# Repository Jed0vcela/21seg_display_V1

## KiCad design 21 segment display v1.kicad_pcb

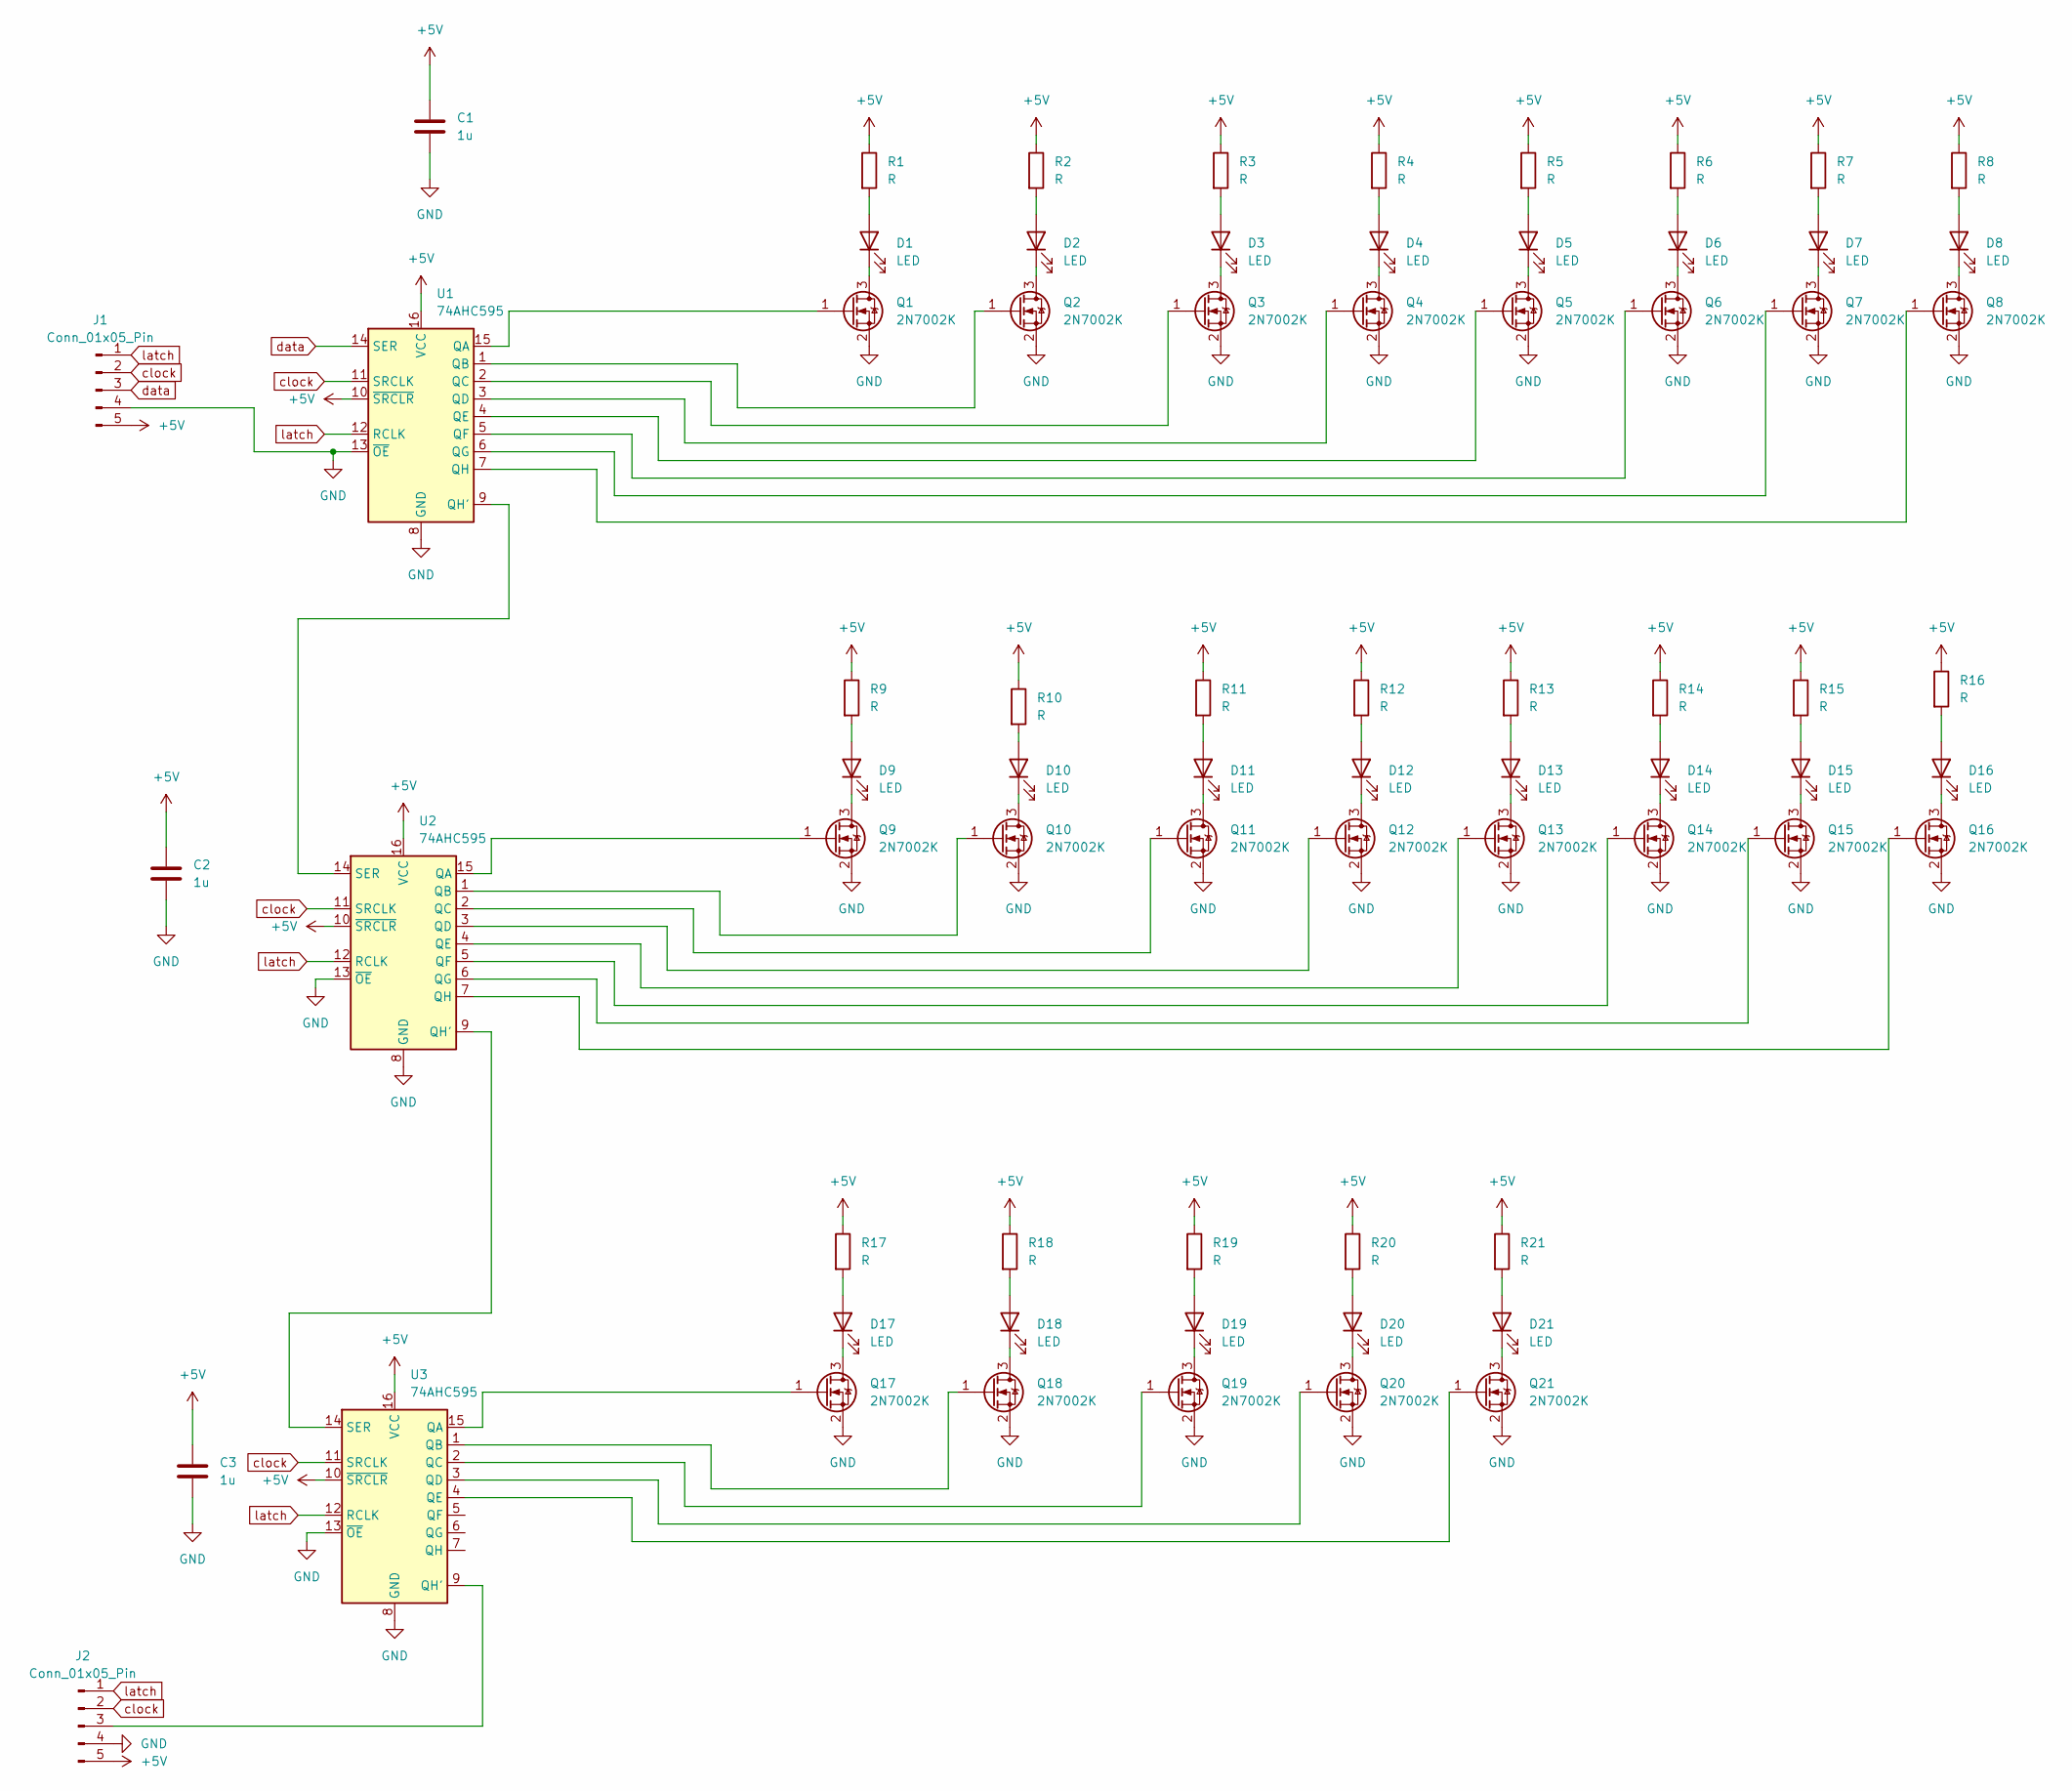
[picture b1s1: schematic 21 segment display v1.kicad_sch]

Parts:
C1, C2, C3: 1u; C_0805_2012Metric
D1, D2, D3, D4, D5, D6, D7, D8, D9, D10, D11, D12, D13, D14, D15, D16, D17, D18, D19, D20, D21: LED; LED_1210_3225Metric_Pad1.42x2.65mm_HandSolder
J1: Conn_01x05_Pin; PinHeader_1x05_P2.54mm_Horizontal
J2: Conn_01x05_Pin; PinSocket_1x05_P2.54mm_Horizontal
Q1, Q2, Q3, Q4, Q5, Q6, Q7, Q8, Q9, Q10, Q11, Q12, Q13, Q14, Q15, Q16, Q17, Q18, Q19, Q20, Q21: 2N7002K; SOT-23
R1, R2, R3, R4, R5, R6, R7, R8, R9, R10, R11, R12, R13, R14, R15, R16, R17, R18, R19, R20, R21: R; R_0805_2012Metric
U1, U2, U3: 74AHC595; SOIC-16_3.9x9.9mm_P1.27mm

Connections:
+5V: C1.1, C2.1, C3.1, J1.5, J2.5, R1.1, R2.1, R3.1, R4.1, R5.1, R6.1, R7.1, R8.1, R9.1, R10.1, R11.1, R12.1, R13.1, R14.1, R15.1, R16.1, R17.1, R18.1, R19.1, R20.1, R21.1, U1.10 (~SRCLR), U1.16 (VCC), U2.10 (~SRCLR), U2.16 (VCC), U3.10 (~SRCLR), U3.16 (VCC)
GND: C1.2, C2.2, C3.2, J1.4, J2.4, Q1.2 (S), Q2.2 (S), Q3.2 (S), Q4.2 (S), Q5.2 (S), Q6.2 (S), Q7.2 (S), Q8.2 (S), Q9.2 (S), Q10.2 (S), Q11.2 (S), Q12.2 (S), Q13.2 (S), Q14.2 (S), Q15.2 (S), Q16.2 (S), Q17.2 (S), Q18.2 (S), Q19.2 (S), Q20.2 (S), Q21.2 (S), U1.8 (GND), U1.13 (~OE), U2.8 (GND), U2.13 (~OE), U3.8 (GND), U3.13 (~OE)
unnamed: D1.2 (A), R1.2
unnamed: D1.1 (K), Q1.3 (D)
unnamed: D2.2 (A), R2.2
unnamed: D2.1 (K), Q2.3 (D)
unnamed: D3.2 (A), R3.2
unnamed: D3.1 (K), Q3.3 (D)
unnamed: D4.2 (A), R4.2
unnamed: D4.1 (K), Q4.3 (D)
unnamed: D5.2 (A), R5.2
unnamed: D5.1 (K), Q5.3 (D)
unnamed: D6.2 (A), R6.2
unnamed: D6.1 (K), Q6.3 (D)
unnamed: D7.2 (A), R7.2
unnamed: D7.1 (K), Q7.3 (D)
unnamed: D8.2 (A), R8.2
unnamed: D8.1 (K), Q8.3 (D)
unnamed: D9.2 (A), R9.2
unnamed: D9.1 (K), Q9.3 (D)
unnamed: D10.2 (A), R10.2
unnamed: D10.1 (K), Q10.3 (D)
unnamed: D11.2 (A), R11.2
unnamed: D11.1 (K), Q11.3 (D)
unnamed: D12.2 (A), R12.2
unnamed: D12.1 (K), Q12.3 (D)
unnamed: D13.2 (A), R13.2
unnamed: D13.1 (K), Q13.3 (D)
unnamed: D14.2 (A), R14.2
unnamed: D14.1 (K), Q14.3 (D)
unnamed: D15.2 (A), R15.2
unnamed: D15.1 (K), Q15.3 (D)
unnamed: D16.2 (A), R16.2
unnamed: D16.1 (K), Q16.3 (D)
unnamed: D17.2 (A), R17.2
unnamed: D17.1 (K), Q17.3 (D)
unnamed: D18.2 (A), R18.2
unnamed: D18.1 (K), Q18.3 (D)
unnamed: D19.2 (A), R19.2
unnamed: D19.1 (K), Q19.3 (D)
unnamed: D20.2 (A), R20.2
unnamed: D20.1 (K), Q20.3 (D)
unnamed: D21.2 (A), R21.2
unnamed: D21.1 (K), Q21.3 (D)
unnamed: J2.3, U3.9 (QH')
unnamed: Q1.1 (G), U1.15 (QA)
unnamed: Q2.1 (G), U1.1 (QB)
unnamed: Q3.1 (G), U1.2 (QC)
unnamed: Q4.1 (G), U1.3 (QD)
unnamed: Q5.1 (G), U1.4 (QE)
unnamed: Q6.1 (G), U1.5 (QF)
unnamed: Q7.1 (G), U1.6 (QG)
unnamed: Q8.1 (G), U1.7 (QH)
unnamed: Q9.1 (G), U2.15 (QA)
unnamed: Q10.1 (G), U2.1 (QB)
unnamed: Q11.1 (G), U2.2 (QC)
unnamed: Q12.1 (G), U2.3 (QD)
unnamed: Q13.1 (G), U2.4 (QE)
unnamed: Q14.1 (G), U2.5 (QF)
unnamed: Q15.1 (G), U2.6 (QG)
unnamed: Q16.1 (G), U2.7 (QH)
unnamed: Q17.1 (G), U3.15 (QA)
unnamed: Q18.1 (G), U3.1 (QB)
unnamed: Q19.1 (G), U3.2 (QC)
unnamed: Q20.1 (G), U3.3 (QD)
unnamed: Q21.1 (G), U3.4 (QE)
unnamed: U1.9 (QH'), U2.14 (SER)
unnamed: U2.9 (QH'), U3.14 (SER)
clock: J1.2, J2.2, U1.11 (SRCLK), U2.11 (SRCLK), U3.11 (SRCLK)
data: J1.3, U1.14 (SER)
latch: J1.1, J2.1, U1.12 (RCLK), U2.12 (RCLK), U3.12 (RCLK)

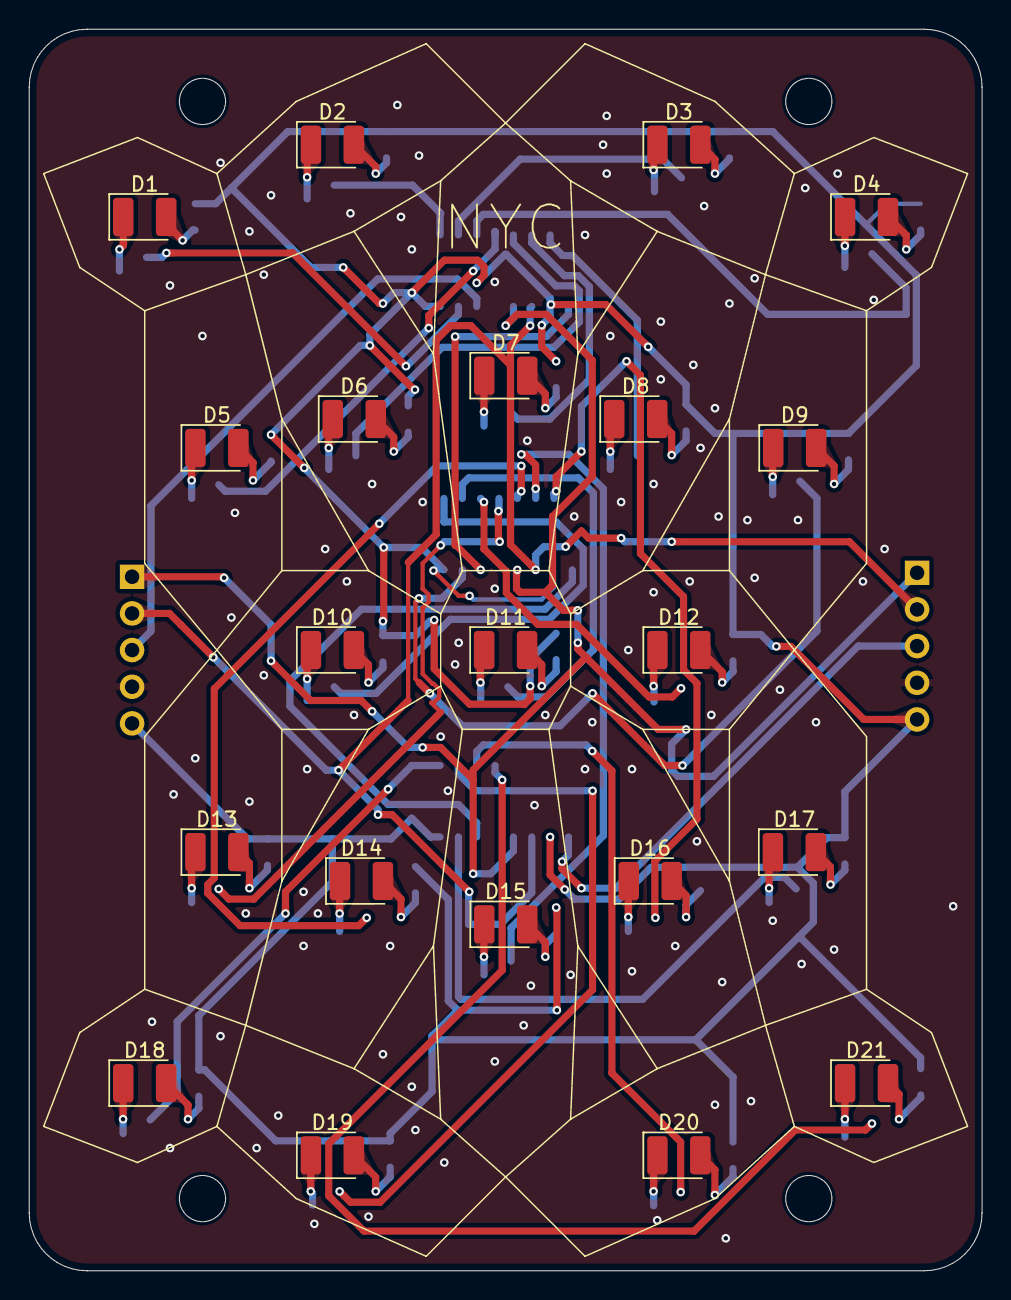
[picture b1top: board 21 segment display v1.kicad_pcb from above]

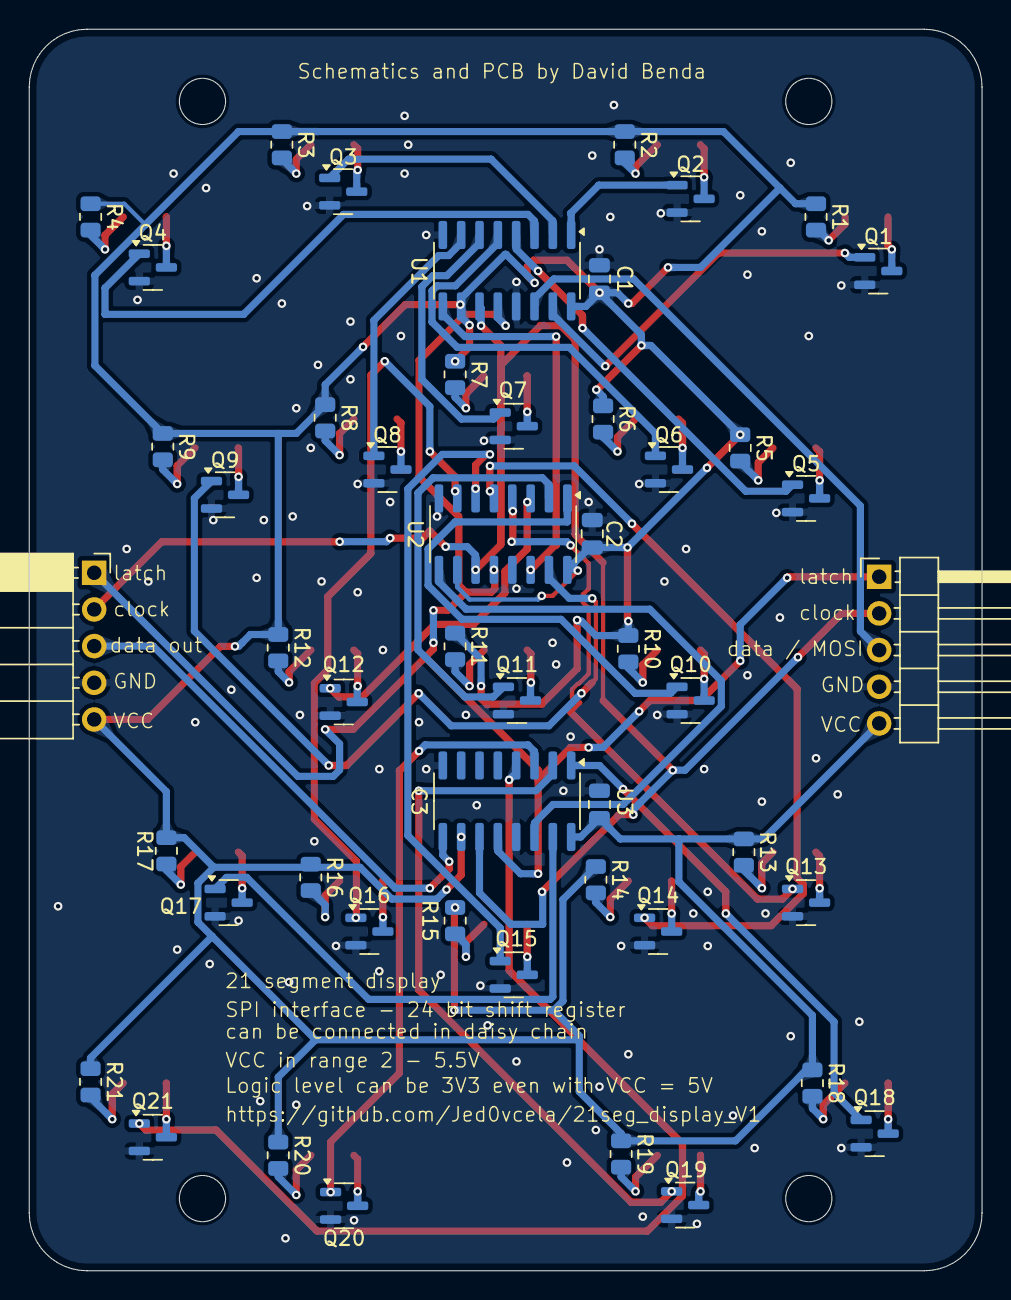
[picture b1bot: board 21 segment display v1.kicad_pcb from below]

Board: 2 copper layers, 66.0 x 86.0 mm, 75 parts (50 on the bottom side), 71 nets.

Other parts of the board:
H1, H2, H3, H4: MountingHole; MountingHole_3.2mm_M3

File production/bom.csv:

Designator,Footprint,Quantity,Value,LCSC Part #
"C1, C2, C3",0805,3,1u,
"D1, D10, D11, D12, D13, D14, D15, D16, D17, D18, D19, D2, D20, D21, D3, D4, D5, D6, D7, D8, D9",1210,21,LED,
J1,PinHeader_1x05_P2.54mm_Horizontal,1,Conn_01x05_Pin,
J2,PinSocket_1x05_P2.54mm_Horizontal,1,Conn_01x05_Pin,
"Q1, Q10, Q11, Q12, Q13, Q14, Q15, Q16, Q17, Q18, Q19, Q2, Q20, Q21, Q3, Q4, Q5, Q6, Q7, Q8, Q9",SOT-23,21,2N7002K,
"R1, R10, R11, R12, R13, R14, R15, R16, R17, R18, R19, R2, R20, R21, R3, R4, R5, R6, R7, R8, R9",0805,21,R,
"U1, U2, U3",SOIC-16_3.9x9.9mm_P1.27mm,3,74AHC595,

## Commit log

2025-11-04 upload
